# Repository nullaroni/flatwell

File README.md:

# Flatwell

A flat, low-profile, wireless keyboard based on the Kinesis Advantage2, laid out like a
MacBook: keys on top, a built-in Apple Magic Trackpad centered below them. It's no bigger than a 16-inch MacBook Pro, so it travels in the
same bag.

- **Layout:** the Advantage2's split key layout with column stagger and no concave wells,
  64 Kailh Choc v1 low-profile switches. No function row; Advantage2-style thumb clusters
  (2u Bksp/Del and Enter/Space, plus Ctrl and End/PgDn) right above the trackpad.
- **Size:** 354 × 247 mm, inside a 16-inch MacBook Pro's footprint (355.7 × 248.1 mm). The
  build fails if it grows past that.
- **Electronics:** our own PCB, a 10 × 7 key matrix wired straight to a nice!nano (17 pins),
  running ZMK.
- **Trackpad:** a whole Magic Trackpad drops into a pocket. (Touch ID is deferred to v2.)
- **Fab:** PCB from PCBWay (Ergogen generates it, KiCad routes it); the case is 3D printed,
  either by PCBWay in one piece per shell or at home in four pieces on a Bambu Lab printer.

Status: **untested v1 prototype**. The board is routed, the firmware builds and the case is
modelled, but nothing has been made yet. What to order is in [ORDER.md](ORDER.md); the design,
decisions and open questions are in [docs/plan.md](docs/plan.md).

## Build

```sh
npm install
npm run build     # → preview/index.html, preview/print.html, output/<variant>/…
                  #   output/macbook/flatwell.kicad_pcb: unrouted PCB, open in KiCad
```

Then route the PCB and make the PCBWay files (needs KiCad, Java and Freerouting; see the
top of `scripts/route.sh`):

```sh
npm run route     # → output/macbook/flatwell-routed.kicad_pcb, fab/macbook/flatwell-gerbers.zip
```

Then the firmware (needs `brew install cmake ninja dtc uv`; first run downloads about 3 GB):

```sh
npm run firmware  # → firmware/flatwell.uf2 (ZMK, with ZMK Studio)
```

And the case shells (needs `uv`):

```sh
npm run case        # → fab/macbook/flatwell-case-{tray,top}.stl       (PCBWay, one piece per shell)
npm run case:bambu  # → fab/macbook/bambu/flatwell-bambu-*.stl         (four pieces for a 256 mm plate)
```

`preview/print.html` prints each half on a Letter page (portrait) at 1:1. Tape the halves
together at the red center line, set a real Magic Trackpad on the outline, and try your
hands on it.

The build fails if:

- a key has no legend or no matrix position, or two keys share a position
- on the PCB, a key's switch and diode aren't wired to each other, or a row or column
  doesn't reach the nice!nano
- a keycap overlaps another key or comes within the rim of the trackpad pocket
- the case outgrows the size limit (`bag_w` × `bag_h`)

- `ergogen/config.yaml`: the parametric layout ([Ergogen](https://ergogen.xyz) v4)
- `ergogen/variants.yaml`: per-variant overrides
- `ergogen/footprints/`: nice!nano (including its 3 middle pins) and back-side SOD-123 diode footprints
- `scripts/build.mjs`: runs Ergogen per variant, places the trackpad, runs the checks,
  renders the previews
- `scripts/legends.mjs`: key legends by key name
- `scripts/case.py`: builds the two case shells from the layout; with `--bambu` it cuts them
  into four pieces that fit a 256 mm printer plate
- `scripts/zmk.mjs`, `scripts/firmware.sh`: generate the ZMK shield in `firmware/` and build it
- `scripts/route.sh`, `scripts/pcb_print.py`, `scripts/kicad_route.py`: autoroute with Freerouting, DRC and fab files via KiCad

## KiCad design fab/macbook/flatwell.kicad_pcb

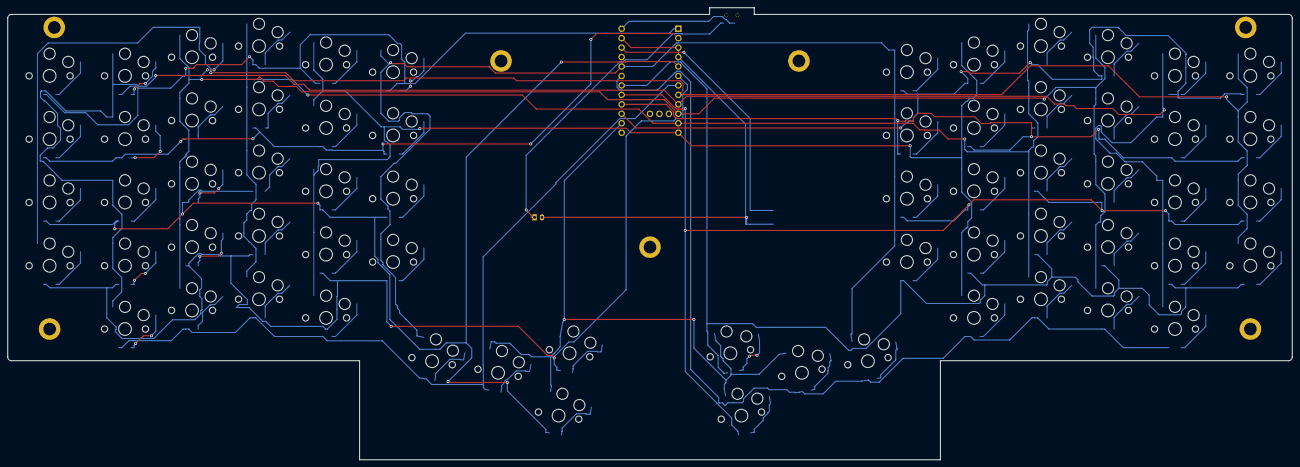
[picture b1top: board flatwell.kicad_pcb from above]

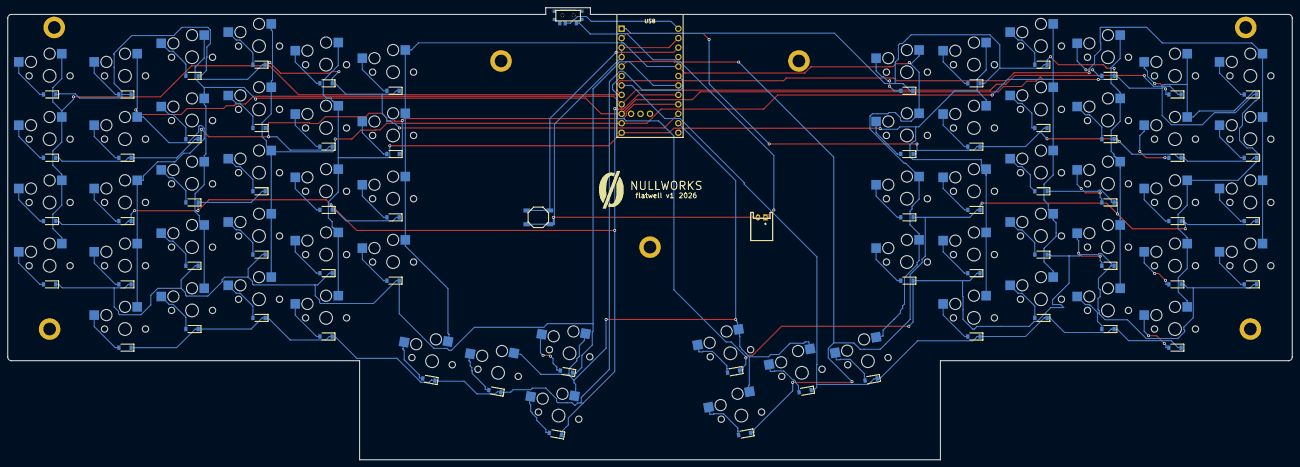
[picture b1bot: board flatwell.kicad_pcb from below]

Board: 2 copper layers, 345.0 x 121.4 mm, 140 parts (66 on the bottom side), 85 nets.

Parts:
B1: SW_TACT_ALPS_SKQGABE010
D1, D2, D3, D4, D5, D6, D7, D8, D9, D10, D11, D12, D13, D14, D15, D16, D17, D18, D19, D20, D21, D22, D23, D24, D25, D26, D27, D28, D29, D30, D31, D32, D33, D34, D35, D36, D37, D38, D39, D40, D41, D42, D43, D44, D45, D46, D47, D48, D49, D50, D51, D52, D53, D54, D55, D56, D57, D58, D59, D60, D61, D62, D63, D64: 1N4148W; D_SOD-123
H1, H2, H3, H4, H5, H6, H7: M3; MountingHole_M3
JST1: JST_PH_S2B-PH-K_02x2.00mm_Angled
LOGO1: Nullworks; Nullworks_Logo
MCU1: nice!nano; nice_nano
S1, S2, S3, S4, S5, S6, S7, S8, S9, S10, S11, S12, S13, S14, S15, S16, S17, S18, S19, S20, S21, S22, S23, S24, S25, S26, S27, S28, S29, S30, S31, S32, S33, S34, S35, S36, S37, S38, S39, S40, S41, S42, S43, S44, S45, S46, S47, S48, S49, S50, S51, S52, S53, S54, S55, S56, S57, S58, S59, S60, S61, S62, S63, S64: PG1350
T1: SPDT_C128955

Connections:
BAT: MCU1.24, T1.2
BAT_IN: JST1.1, T1.1
C0: MCU1.8, S1.1, S2.1, S3.1, S4.1, S33.1, S34.1, S35.1, S36.1
C1: MCU1.9, S5.1, S6.1, S7.1, S8.1, S9.1, S37.1, S38.1, S39.1, S40.1, S41.1
C2: MCU1.10, S10.1, S11.1, S12.1, S13.1, S14.1, S42.1, S43.1, S44.1, S45.1, S46.1
C3: MCU1.11, S15.1, S16.1, S17.1, S18.1, S19.1, S47.1, S48.1, S49.1, S50.1, S51.1
C4: MCU1.12, S20.1, S21.1, S22.1, S23.1, S24.1, S52.1, S53.1, S54.1, S55.1, S56.1
C5: MCU1.20, S25.1, S26.1, S27.1, S28.1, S29.1, S57.1, S58.1, S59.1, S60.1, S61.1
C6: MCU1.14, S30.1, S31.1, S32.1, S62.1, S63.1, S64.1
GND: B1.2, JST1.2, MCU1.3, MCU1.4, MCU1.23
R0: D4.1, D9.1, D14.1, D19.1, D24.1, D28.1, MCU1.1
R1: D3.1, D8.1, D13.1, D18.1, D23.1, D27.1, MCU1.2
R2: D2.1, D7.1, D12.1, D17.1, D22.1, D26.1, D31.1, MCU1.5
R3: D1.1, D6.1, D11.1, D16.1, D21.1, D25.1, D32.1, MCU1.6
R4: D5.1, D10.1, D15.1, D20.1, D29.1, D30.1, MCU1.7
R5: D36.1, D41.1, D46.1, D51.1, D56.1, D60.1, MCU1.15
R6: D35.1, D40.1, D45.1, D50.1, D55.1, D59.1, MCU1.16
R7: D34.1, D39.1, D44.1, D49.1, D54.1, D58.1, D63.1, MCU1.17
R8: D33.1, D38.1, D43.1, D48.1, D53.1, D57.1, D64.1, MCU1.18
R9: D37.1, D42.1, D47.1, D52.1, D61.1, D62.1, MCU1.19
RST: B1.1, MCU1.22
matrix_index_bottom: D20.2, S20.2
matrix_index_home: D22.2, S22.2
matrix_index_num: D24.2, S24.2
matrix_index_top: D23.2, S23.2
matrix_index_zrow: D21.2, S21.2
matrix_inner_home: D26.2, S26.2
matrix_inner_num: D28.2, S28.2
matrix_inner_top: D27.2, S27.2
matrix_inner_zrow: D25.2, S25.2
matrix_middle_bottom: D15.2, S15.2
matrix_middle_home: D17.2, S17.2
matrix_middle_num: D19.2, S19.2
matrix_middle_top: D18.2, S18.2
matrix_middle_zrow: D16.2, S16.2
matrix_outer_home: D2.2, S2.2
matrix_outer_num: D4.2, S4.2
matrix_outer_top: D3.2, S3.2
matrix_outer_zrow: D1.2, S1.2
matrix_pinky_bottom: D5.2, S5.2
matrix_pinky_home: D7.2, S7.2
matrix_pinky_num: D9.2, S9.2
matrix_pinky_top: D8.2, S8.2
matrix_pinky_zrow: D6.2, S6.2
matrix_ring_bottom: D10.2, S10.2
matrix_ring_home: D12.2, S12.2
matrix_ring_num: D14.2, S14.2
matrix_ring_top: D13.2, S13.2
matrix_ring_zrow: D11.2, S11.2
mirror_matrix_index_bottom: D52.2, S52.2
mirror_matrix_index_home: D54.2, S54.2
mirror_matrix_index_num: D56.2, S56.2
mirror_matrix_index_top: D55.2, S55.2
mirror_matrix_index_zrow: D53.2, S53.2
mirror_matrix_inner_home: D58.2, S58.2
mirror_matrix_inner_num: D60.2, S60.2
mirror_matrix_inner_top: D59.2, S59.2
mirror_matrix_inner_zrow: D57.2, S57.2
mirror_matrix_middle_bottom: D47.2, S47.2
mirror_matrix_middle_home: D49.2, S49.2
mirror_matrix_middle_num: D51.2, S51.2
mirror_matrix_middle_top: D50.2, S50.2
mirror_matrix_middle_zrow: D48.2, S48.2
mirror_matrix_outer_home: D34.2, S34.2
mirror_matrix_outer_num: D36.2, S36.2
mirror_matrix_outer_top: D35.2, S35.2
mirror_matrix_outer_zrow: D33.2, S33.2
mirror_matrix_pinky_bottom: D37.2, S37.2
mirror_matrix_pinky_home: D39.2, S39.2
mirror_matrix_pinky_num: D41.2, S41.2
mirror_matrix_pinky_top: D40.2, S40.2
mirror_matrix_pinky_zrow: D38.2, S38.2
mirror_matrix_ring_bottom: D42.2, S42.2
mirror_matrix_ring_home: D44.2, S44.2
mirror_matrix_ring_num: D46.2, S46.2
mirror_matrix_ring_top: D45.2, S45.2
mirror_matrix_ring_zrow: D43.2, S43.2
mirror_thumb_bspc_low: D61.2, S61.2
mirror_thumb_del_low: D62.2, S62.2
mirror_thumb_nav_high: D64.2, S64.2
mirror_thumb_nav_low: D63.2, S63.2
thumb_bspc_low: D29.2, S29.2
thumb_del_low: D30.2, S30.2
thumb_nav_high: D32.2, S32.2
thumb_nav_low: D31.2, S31.2
